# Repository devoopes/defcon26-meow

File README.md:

# DEFCON 26 - Maneki-neko Badge

photo by [Roberto Baldwin](https://twitter.com/@strngwys)  

Follow the Twitter for updates [@ManekiNekoDC](https://twitter.com/ManekiNekoDC)  

We went to DEF CON 26 and launched an unofficial DEF CON badge. We wanted to be able to create something different and unique to some of the other designs out there. The badge is controlled by an STM32 that drives the servo and dual 16 segment LEDS on the front. We attached a 3d printed arm to the servo. All the files are source code are Open Source and in this repo. You are welcome to make one yourself via OSHpark or JLC PCB. Gerber files are located in the repo.  

### Art Design:
Our art was done by Jeff Chang.
http://www.jeffchangart.com/  
Twitter [@jeffchangart](https://twitter.com/jeffchangart)  
Instagram [@jeffchangart](https://instagram.com/jeffchangart)  

All the drafts, and formats of the art can be found in the /art/ directory.

Lanyards were done by https://customlanyards4all.com

### Meowtronics

First done with KiCAD but abandoned after more experienced help was provided. <3 \
You can find all the Eagle files in the [eagle directory](https://github.com/SeanLeftBelow/defcon26-meow/tree/master/pcb/eagle).

Board is on [OSHpark](https://oshpark.com/shared_projects/X3Hxcson)

Guide is [here](https://github.com/SeanLeftBelow/defcon26-meow/tree/master/guide)

First look at the boards from the fab house.  

### SAO (Special Addons/ Shitty Addons)

Overall design is a copy of the main badge. See writeup [here](https://github.com/SeanLeftBelow/defcon26-meow/tree/master/addon)

### In The Mews

[Engadget: This cute Def Con badge beckons you to hack  it](https://www.engadget.com/2018/08/15/this-cute-def-con-badge-beckons-you-to-hack-it/  ) \
[Hackaday: ALL THE BADGES OF DEF CON 26 (VOL 1)](https://hackaday.com/2018/08/14/all-the-badges-of-def-con-26-vol-1/) \
[BadgeLife - A Hackaday Documentary](https://www.youtube.com/watch?v=G2fHKRONc6U) \

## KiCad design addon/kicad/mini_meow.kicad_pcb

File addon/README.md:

# Overview
This folder contains the in-progress files for a Maneki-Neko "Simple* Add-On" as per the [Simple Add-On Standard](https://hackaday.com/2018/06/21/this-is-the-year-conference-badges-get-their-own-badges/).

**Note** Documentation is still in progress

BIG Thank You's go to [Contextual Electronics](https://www.youtube.com/channel/UCkJRycUz2CylxpiP-zMePow) for the YouTube Getting to Blinky Series.

This was the most useful tutorial that I referred to while going through the process. If you have the opportunity to read or watch through the entire thing before starting, I highly recommend it as this gives you a fair amount of context.

# Making the Add-On!

1. Create Project
Open KiCad and create a new project. A blank layout and schematic will be created when you create the project.

2. Open Schematic
There are many ways to do this. You can:

- Double-click the .sch file
- Click the Eeschema Launcher shortcut
- Click Command + E
- Go to Tools --> Run Eeschema

3. Create Library and Library Items
- Open Library Editor
- Create component for the connector

4. Build Schematic
- Open Schematic Editor
- Add components to the schematic: LEDs, Resistors, Connector
- Add wiring for components
- Annotate schematic
- Run Error Rule Checking

5. Create Net List

6. Create Layout
- Run PCBNew to create layout
- Go back to Schematic Editor
- Click icon for CvPcb to associate schematic components with component footprints for Layout

7. Add Footprint for Add-on connector
- Go to Footprint Editor
- Add Footprint
- Save footprint to new library
- Add Footprint Libraries Wizard

8. Layout PCB
- Layout components so that ratsnest wires do not cross connect

9. Define Edge Cut layer
(prepare for frustration, desperation, time loss, or maybe everything just goes according to plan!)
- Create DXF file for Import based on solid outline
- @TODO add details on best practices for creating a good DXF for import
- Note that dimensions should match

10. Import Silkscreen Image
- Create silkscreen as footprint and import using BMP to Component tool
- @TODO add details
- There may be some trial and error to get the dimensions to match
- 1000x1000 px resolution png with inverted colors ended up with the best results (light image dark background)
- Import to silk layer

11. Setup Copper Layers
- Create copper layers as individual images and import using BMP to Component tool
- @TODO add details
- There may be some trial and error to get the dimensions to match
- 1000x1000 px resolution png with inverted colors ended up with the best results (light image dark background)
- Import to .... F.Cu layer?

NOTES:
- The program assumes arbitrary input resolution of 300ppi, so a 300 by 300 image will give a 1" by 1" logo on the board.
- According to Best Practices, minimize the number of right angles as you layout the tracks/traces between components on your board.

Want to learn more about PCB Layout and solder mask?
https://learn.sparkfun.com/tutorials/pcb-basics/composition
https://learn.sparkfun.com/tutorials/beginners-guide-to-kicad/editing-a-pcb-layout

Other Resources and Links:
https://medium.com/@urish/a-practical-guide-to-designing-pcb-art-b5aa22926a5c

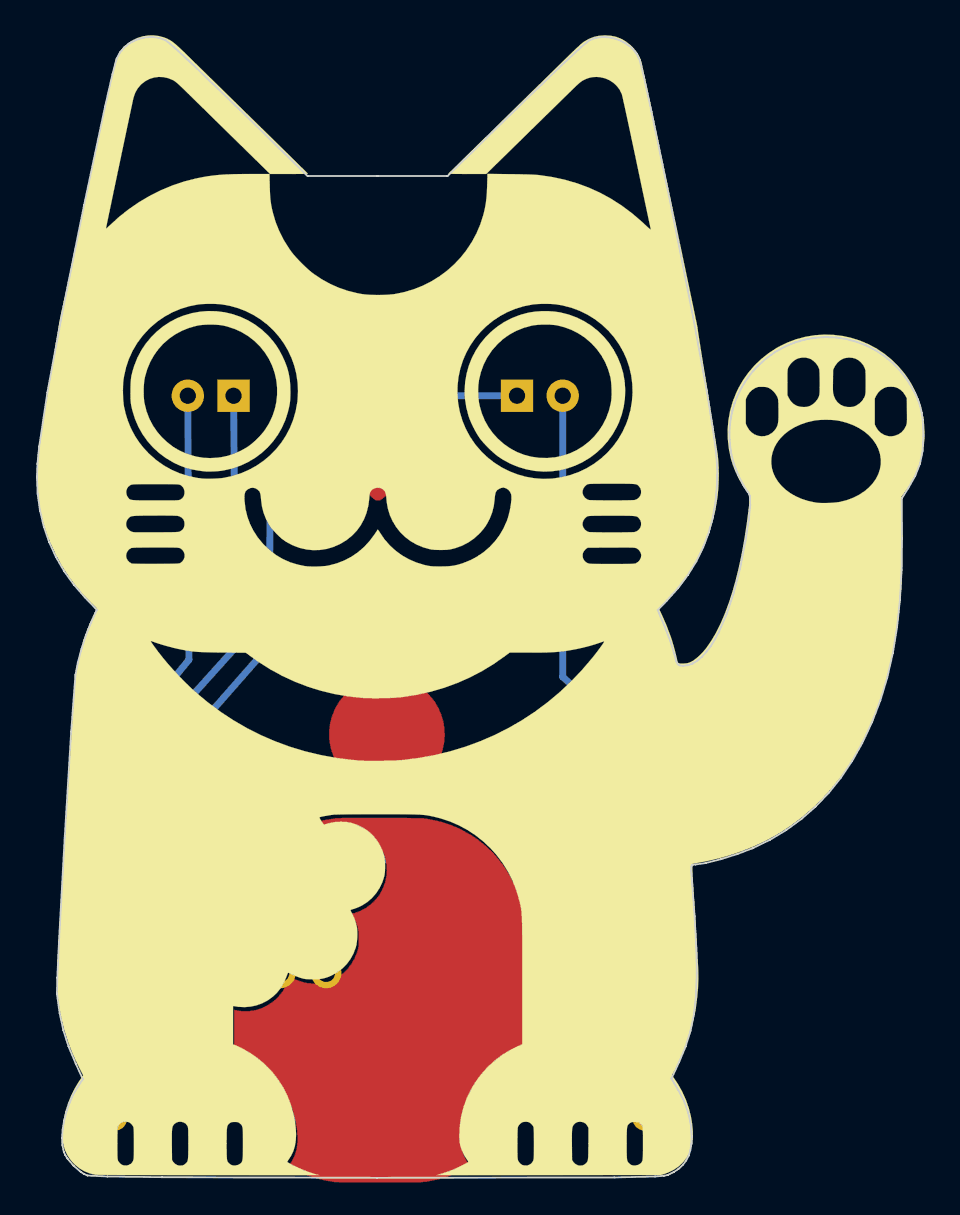
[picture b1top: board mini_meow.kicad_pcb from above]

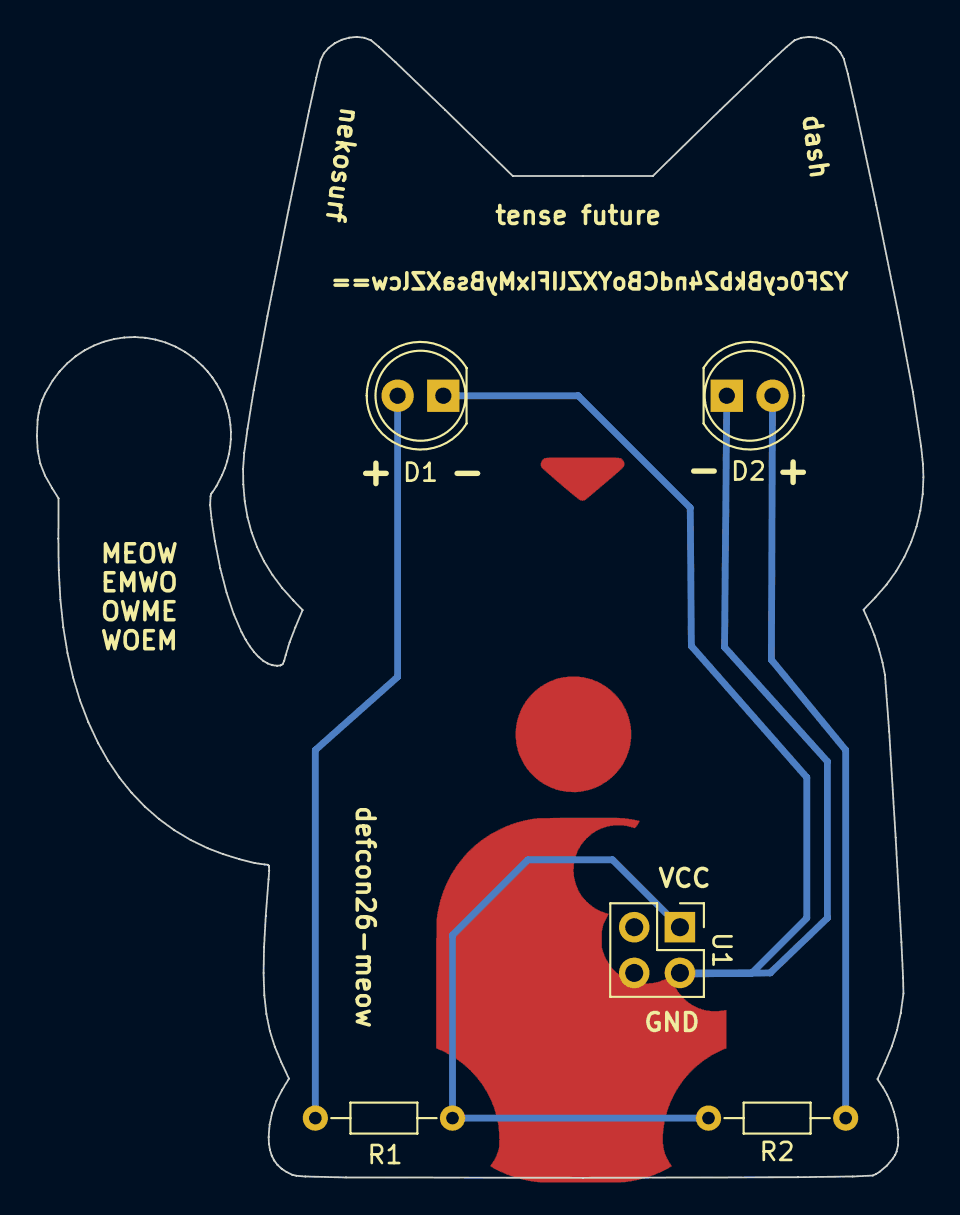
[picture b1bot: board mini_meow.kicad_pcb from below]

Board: 2 copper layers, 49.3 x 63.4 mm, 5 parts (5 on the bottom side), 4 nets.

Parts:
D1, D2: LED; LED_D5.0mm
R1, R2: 65; R_Axial_DIN0204_L3.6mm_D1.6mm_P7.62mm_Horizontal
U1: sa_connector; Pin_Header_Straight_2x02_Pitch2.54mm

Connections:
+3V3: R1.2, R2.2, U1.1
GND: D1.1, D2.1, U1.2
unnamed: D1.2, R1.1
unnamed: D2.2, R2.1

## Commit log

2018-03-23 First art asset
2018-03-23 rotated
2018-05-25 meow.svg v1
    Adding first pass of meow SVG
2018-05-25 Finished base of v1
    Its aweful
2018-05-25 Trying some other samples
2018-05-25 Ok, im starting to be happy with this.
2018-05-25 adding osh
2018-05-25 Some older stuff
2018-05-25 Updates to move computers.
2018-05-25 Typo
2018-06-04 Adding Art and kiCAD
2018-06-09 initial commit of eagle files, schematics 95%
2018-06-09 adding eagle local backup files to .gitignore
2018-06-09 adding libraries i built or found, not part of stock eagle install
2018-06-10 board outline in, some minor edits to schematic, board ready for component placement
2018-06-11 some component placement, eyes locked in
2018-06-13 more layout. changed out connectors to support a clean 'art' (top) side. shooting for 2 layers, might need to be 4 to avoid a ton of routing time.
2018-06-14 completely regretting my decision to use eagle
2018-06-14 mini commit before taking a shower and letting autorouter mess around
2018-06-15 re-orging traces to eyes for clean routing, done routing left eye
2018-06-17 all led and high(er) speed signals routed... phewf
2018-06-18 pcb traces routed, just need to finish off GND and 3V3 rails
2018-06-20 finished routing incl 3v3 and gnd, except shitty addon connector (will route after artwork is added
2018-06-23 update gitignore, add intermediate art files, update layout file
2018-06-24 added copper art (nose, collar tag, and coin). just need to route shitty addon connector and i think its done
2018-06-25 silk fixed, drc errors fixed, going to export and send thru freedfm
2018-06-26 updated design (smt servo connector), out to freedfm, quote from seeed
2018-06-27 adjusted ref des line thickness, created fab/assy pkg for vendor RFQs. this might be the final form....
2018-06-27 added power switch and user button
2018-06-29 OUT TO FAB OMG 2560256025602560
2018-07-06 Cleanup
2018-07-11 adding in-progress for mini-meow add-on
2018-07-11 removed DS_Store
2018-07-12 added ground
2018-07-13 added net list, updated schematic, layout
2018-07-14 moved back from 2 resistors to 1
2018-07-19 updated kicad for new layout
2018-07-22 blank new project for stm32f030_8 (we are using c8t6)
2018-07-22 typo in .gitignore, Object/ => Objects/
2018-07-22 exported from illustrator
2018-07-23 Adding files for kicad import ease
2018-07-23 Made into 1 object
2018-07-24 Adding README back and some photos
2018-07-24 Updating
2018-07-25 pcb update, added working art files
2018-07-25 added -bak to gitignore
2018-07-25 updated library, added copper images
2018-07-25 BOM stuff
2018-07-25 updated pcb, maybe first final draft
2018-07-26 updated copper layers. added ground
2018-07-26 updated copper layers....again...
2018-07-26 updated some silkscreen text
2018-07-26 updated mask for copper
2018-07-26 Adding non gray version
2018-07-27 added gerber files
2018-07-27 Blender Files
2018-07-27 1.5 test
2018-07-27 Updating osh rev
2018-07-27 Cleanup and adding v2
2018-07-28 ignore updates, blank firmware template update, pcb paw fix (coin cutout for paw)
2018-07-28 led test implemented in firmware. dunno why the whitesilk svg changed but committing anyway.
2018-07-31 deleting files, will replace with new. accidentally been working from a different diretory.
2018-07-31 cubemx project generator included all kinds of unnecessary library files but im too lazy to work through them and write instructions on how to install dependencies so just deal with it.
2018-07-31 interrupt working, trying to make it trigger waving animation, but interrupt handler doesnt like calling user functions 2 deep for some reason (or something else im not catching)
2018-08-01 timed blink and paw wave animation, kind of interrupt based
2018-08-01 MVP candidate 1. commit all the things i dont care apparently i dont know how gitignore works whatever
2018-08-02 Arm (#3)
    * Blender Files
    * 1.5 test
    * Cleanup and adding v2
2018-08-02 BOM stuff (#4)
2018-08-02 Adding 3d files
2018-08-07 60 seconds and servo fix.
2018-08-11 update oshpark link
2018-08-15 Adding Twitter to README
2018-08-15 Fixing formating and adding more info
2018-08-15 update oshpark link (#5)
2018-08-16 commit cost reduction study text doc pt 1, moar updates tmrw
2018-08-18 created SAO Rev2 with correct connector orientation
2018-08-18 updated kicad to display layers and fix silk rotation
2018-08-18 Cleanup and README update
2018-08-18 Formatting issue
2018-08-18 More pictures
2018-08-18 Art (#6)
    * created SAO Rev2 with correct connector orientation
    * updated kicad to display layers and fix silk rotation
2018-08-18 rearranged art directory
2018-08-18 le formating sigh
2018-08-18 Lanyard stuff
2018-08-20 wrong image
2018-08-20 Delete lanyards.jpg
    Not updating.
2018-08-20 Fixing lanyard image
2018-09-05 version 2 start, cost reduction edits to schematic
2018-09-17 pcb v2 routed, bom edited, gerbers rendered - quote out to pcba house and dfm check to freedfm
2018-10-21 First rev of the guide
2018-10-21 jpg --> JPG
2018-10-21 width resize
2018-10-23 Wrap up for the guide
2018-10-23 Final typo check
2018-10-23 Final touches
2018-10-23 Werid md format thing
2018-10-23 Final draft
2018-10-23 Create LICENSE
2018-10-28 revised gerbers
2018-10-29 revised gerbers (#8)
